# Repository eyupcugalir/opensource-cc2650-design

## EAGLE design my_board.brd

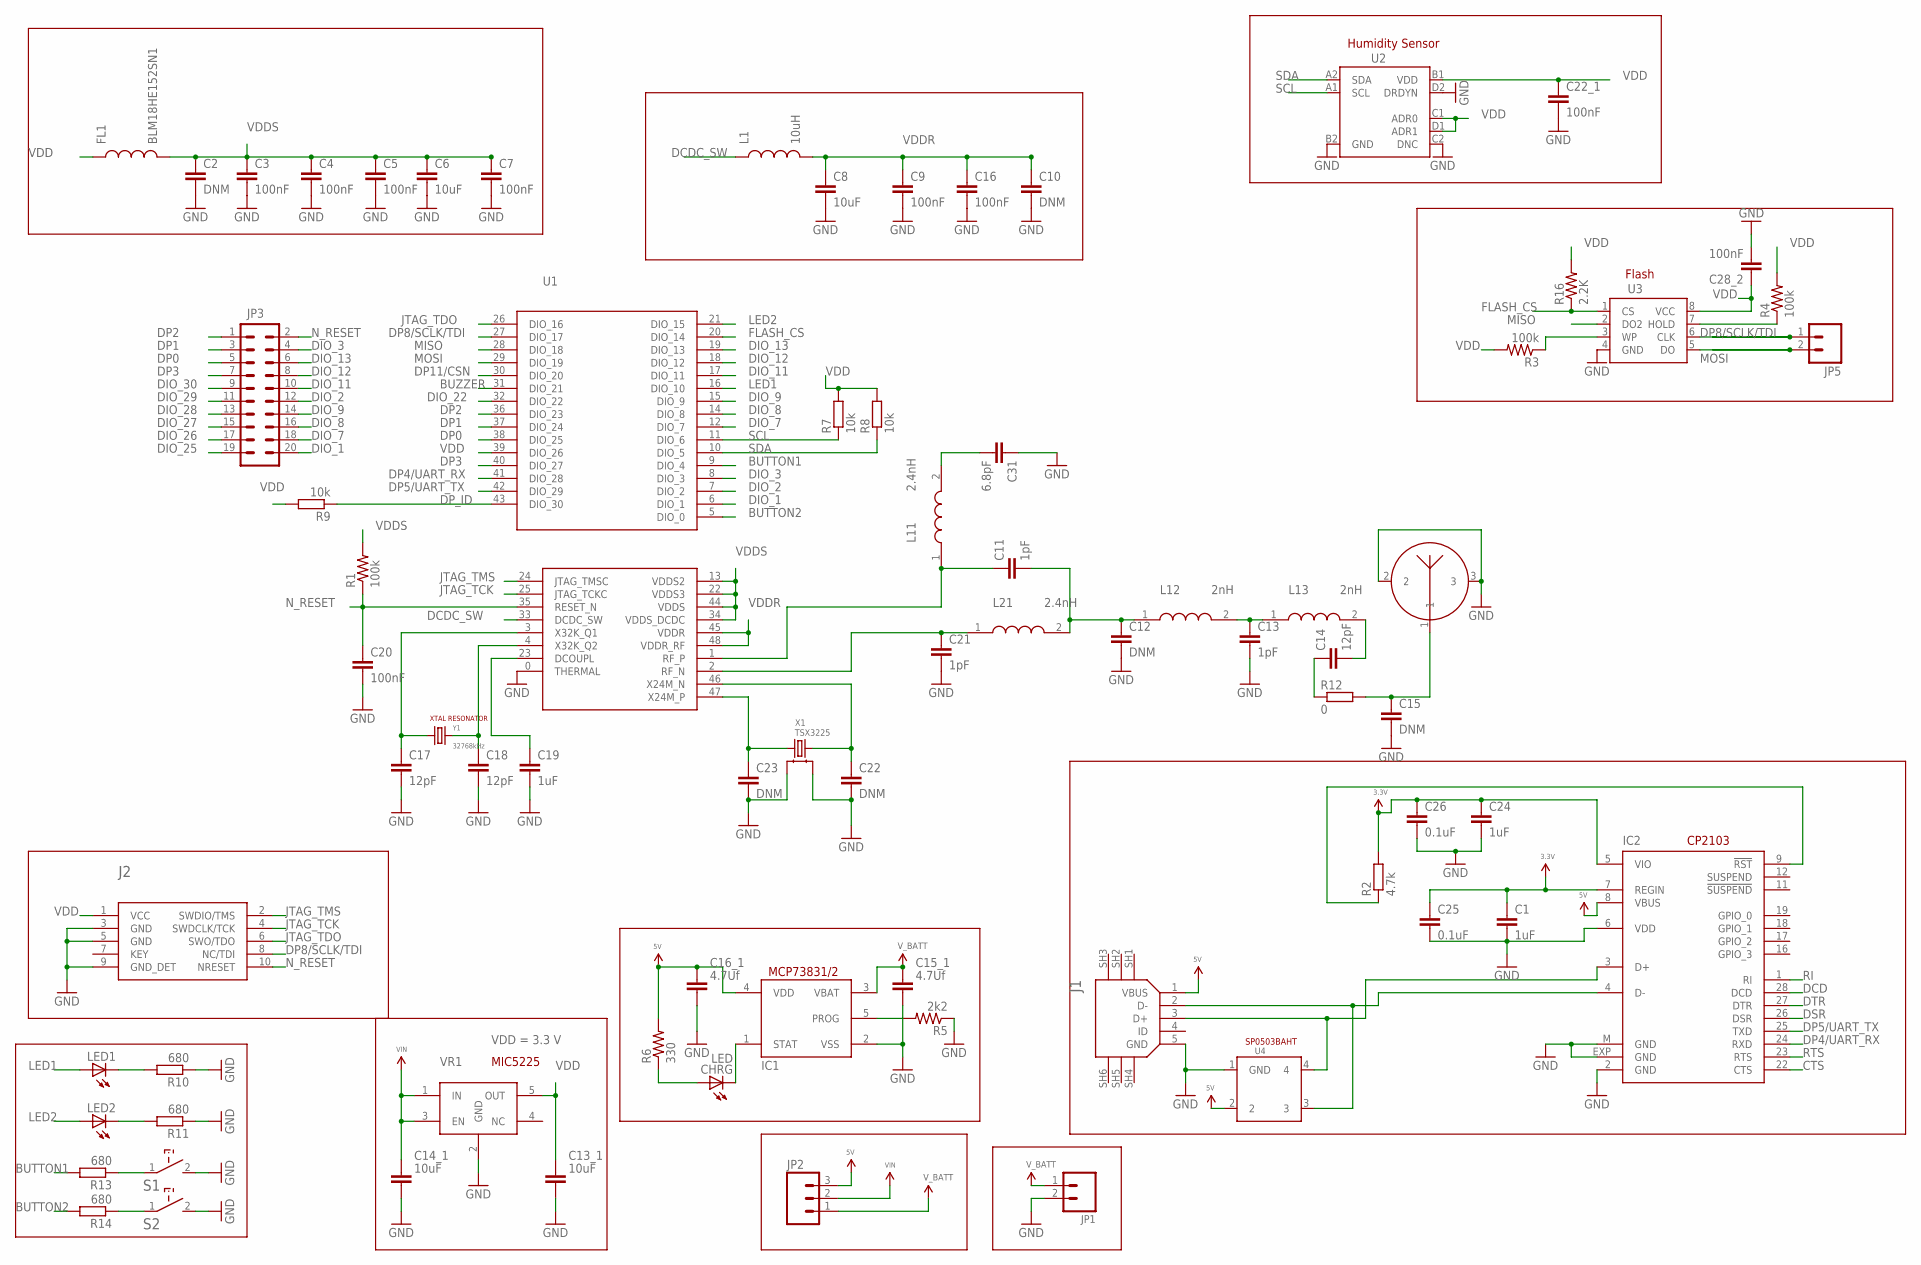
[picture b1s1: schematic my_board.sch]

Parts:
C1, C19, C24: 1uF; 0402-CAP
C2: DNM; 0603-CAP
C3, C4, C5, C9, C16, C20, C22_1, C28_2: 100nF; 0402-CAP
C6, C8: 10uF; 0603-CAP
C7: 100nF; 0603-CAP
C10, C12, C15, C22, C23: DNM; 0402-CAP
C11, C13, C21: 1pF; 0402-CAP
C13_1, C14_1: 10uF; DP_DEVICES_C603
C14, C17, C18: 12pF; 0402-CAP
C15_1, C16_1: 4.7Uf; DP_DEVICES_C603
C25, C26: 0.1uF; 0402-CAP
C31: 6.8pF; 0402-CAP
CHRG: LED; DP_DEVICES_LED-603
FL1: BLM18HE152SN1; 0603
IC1: ADAFRUIT_MCP73831/OT; ADAFRUIT_SOT23-5L
IC2: CP2103_USB_UART; MLP28
J1: USB-1981568; 1981568-1
J2: ARM-10PIN-JTAG; ARM-10PIN-DEBUGGER
JP1: SPARKFUN-CONNECTORS_M02PTH3; SPARKFUN-CONNECTORS_1X02_LONGPADS
JP2: M03-SCREW-5MM; SCREWTERMINAL-5MM-3
JP3: M10X2; 2X10
JP5: M02PTH; 1X02
L1: 10uH; 0805
L11, L21: 2.4nH; LQG15HS2N4S02D
L12, L13: 2nH; LQG15HS2N4S02D
LED1, LED2: DP_DEVICES_LED-0805; DP_DEVICES_LED-805
R1, R3, R4: 100k; 0402-RES
R2: 4.7k; R0402
R5: 2k2; SPARKFUN-RESISTORS_0805
R6: 330; SPARKFUN-RESISTORS_0805
R7, R8, R9: 10k; R0402
R10, R11, R13, R14: 680; R0402
R12: 0; R0402
R16: 2.2K; 0402-RES
S1, S2: B3U-1000P-SWITCH
U1: CC2650
U2: HDC1000YPA
U3: W25X40CLUXIGSS; W25X40SSIG
U4: SP0503BAHT
U$1: PCB-ANTENNA
VR1: USBUG_MIC5225-3.3YM5; USBUG_SOT23-5
X1: TSX3225; TSX-3225
Y1: 32768kHz; CRYSTAL_RESONATOR

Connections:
3.3V: C1.1, C24.1, C25.1, C26.1, IC2.5 (VIO), IC2.7 (REGIN), R2.2
5V: C16_1.1, IC1.4 (VDD), IC2.8 (VBUS), J1.1 (VBUS), JP2.3, R6.2, U4.2
BUTTON1: R13.2, U1.9 (DIO_4)
BUTTON2: R14.2, U1.5 (DIO_0)
BUZZER: U1.31 (DIO_21)
CTS: IC2.22 (CTS)
DCD: IC2.28 (DCD)
DCDC_SW: L1.1, U1.33 (DCDC_SW)
DIO_1: JP3.20, U1.6 (DIO_1)
DIO_2: JP3.12, U1.7 (DIO_2)
DIO_3: JP3.4, U1.8 (DIO_3)
DIO_7: JP3.18, U1.12 (DIO_7)
DIO_8: JP3.16, U1.14 (DIO_8)
DIO_9: JP3.14, U1.15 (DIO_9)
DIO_11: JP3.10, U1.17 (DIO_11)
DIO_12: JP3.8, U1.18 (DIO_12)
DIO_13: JP3.6, U1.19 (DIO_13)
DIO_22: U1.32 (DIO_22)
DIO_25: JP3.19
DIO_26: JP3.17
DIO_27: JP3.15
DIO_28: JP3.13
DIO_29: JP3.11
DIO_30: JP3.9
DP0: JP3.5, U1.38 (DIO_25)
DP1: JP3.3, U1.37 (DIO_24)
DP2: JP3.1, U1.36 (DIO_23)
DP3: JP3.7, U1.40 (DIO_27)
DP4/UART_RX: IC2.24 (RXD), U1.41 (DIO_28)
DP5/UART_TX: IC2.25 (TXD), U1.42 (DIO_29)
DP8/SCLK/TDI: J2.8 (NC/TDI), JP5.1, U1.27 (DIO_17), U3.6 (CLK)
DP11/CSN: U1.30 (DIO_20)
DP_ID: R9.1, U1.43 (DIO_30)
DSR: IC2.26 (DSR)
DTR: IC2.27 (DTR)
FLASH_CS: R16.1, U1.20 (DIO_14), U3.1 (CS)
GND: C1.2, C2.2, C3.2, C4.2, C5.2, C6.2, C7.2, C8.2, C9.2, C10.2, C12.2, C13.2, C13_1.2, C14_1.2, C15.2, C15_1.2, C16.2, C16_1.2, C17.2, C18.2, C19.2, C20.2, C21.2, C22.2, C22_1.2, C23.2, C24.2, C25.2, C26.2, C28_2.2, C31.1, IC1.2 (VSS), IC2.2 (GND), IC2.6 (VDD), IC2.EXP (GND), IC2.M (GND), J1.5 (GND), J2.3 (GND), J2.5 (GND), J2.9 (GND_DET), JP1.2, R5.1, R10.1, R11.1, S1.2, S2.2, U1.0 (THERMAL), U2.B2 (GND), U2.C2 (DNC), U2.D2 (DRDYN), U3.4 (GND), U4.1 (GND), U$1.2, U$1.3, VR1.2 (GND), X1.2, X1.4
JTAG_TCK: J2.4 (SWDCLK/TCK), U1.25 (JTAG_TCKC)
JTAG_TDO: J2.6 (SWO/TDO), U1.26 (DIO_16)
JTAG_TMS: J2.2 (SWDIO/TMS), U1.24 (JTAG_TMSC)
LED1: LED1.A, U1.16 (DIO_10)
LED2: LED2.A, U1.21 (DIO_15)
MISO: U1.28 (DIO_18), U3.2 (DO2)
MOSI: JP5.2, U1.29 (DIO_19), U3.5 (DO)
unnamed: C31.2, L11.2
unnamed: C17.1, U1.3 (X32K_Q1), Y1.P$1 (1)
unnamed: C18.1, U1.4 (X32K_Q2), Y1.P$4 (2)
unnamed: C14.2, L13.2
unnamed: C22.1, U1.46 (X24M_N), X1.3
unnamed: C11.2, C12.1, L12.1, L21.2
unnamed: CHRG.A, R6.1
unnamed: C13.1, L12.2, L13.1
unnamed: C14.1, R12.1
unnamed: C15.1, R12.2, U$1.1
unnamed: C23.1, U1.47 (X24M_P), X1.1
unnamed: CHRG.C, IC1.1 (STAT)
unnamed: C11.1, L11.1, U1.1 (RF_P)
unnamed: C21.1, L21.1, U1.2 (RF_N)
unnamed: IC1.5 (PROG), R5.2
unnamed: C19.1, U1.23 (DCOUPL)
unnamed: LED1.C, R10.2
unnamed: R3.1, U3.3 (WP)
unnamed: R4.1, U3.7 (HOLD)
unnamed: IC2.3 (D+), J1.3 (D+), U4.4
unnamed: IC2.4 (D-), J1.2 (D-), U4.3
unnamed: LED2.C, R11.2
unnamed: IC2.9 (!RST), R2.1
unnamed: R13.1, S1.1
unnamed: R14.1, S2.1
N_RESET: C20.1, J2.10 (NRESET), JP3.2, R1.1, U1.35 (RESET_N)
RI: IC2.1 (RI)
RTS: IC2.23 (RTS)
SCL: R7.1, U1.11 (DIO_6), U2.A1 (SCL)
SDA: R8.1, U1.10 (DIO_5), U2.A2 (SDA)
VDD: C13_1.1, C22_1.1, C28_2.1, FL1.1, J2.1 (VCC), R3.2, R4.2, R7.2, R8.2, R9.2, R16.2, U1.39 (DIO_26), U2.B1 (VDD), U2.C1 (ADR0), U2.D1 (ADR1), U3.8 (VCC), VR1.5 (OUT)
VDDR: C8.1, C9.1, C10.1, C16.1, L1.2, U1.45 (VDDR), U1.48 (VDDR_RF)
VDDS: C2.1, C3.1, C4.1, C5.1, C6.1, C7.1, FL1.2, R1.2, U1.13 (VDDS2), U1.22 (VDDS3), U1.34 (VDDS_DCDC), U1.44 (VDDS)
VIN: C14_1.1, JP2.2, VR1.1 (IN), VR1.3 (EN)
V_BATT: C15_1.1, IC1.3 (VBAT), JP1.1, JP2.1

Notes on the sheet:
VDD = 3.3 V

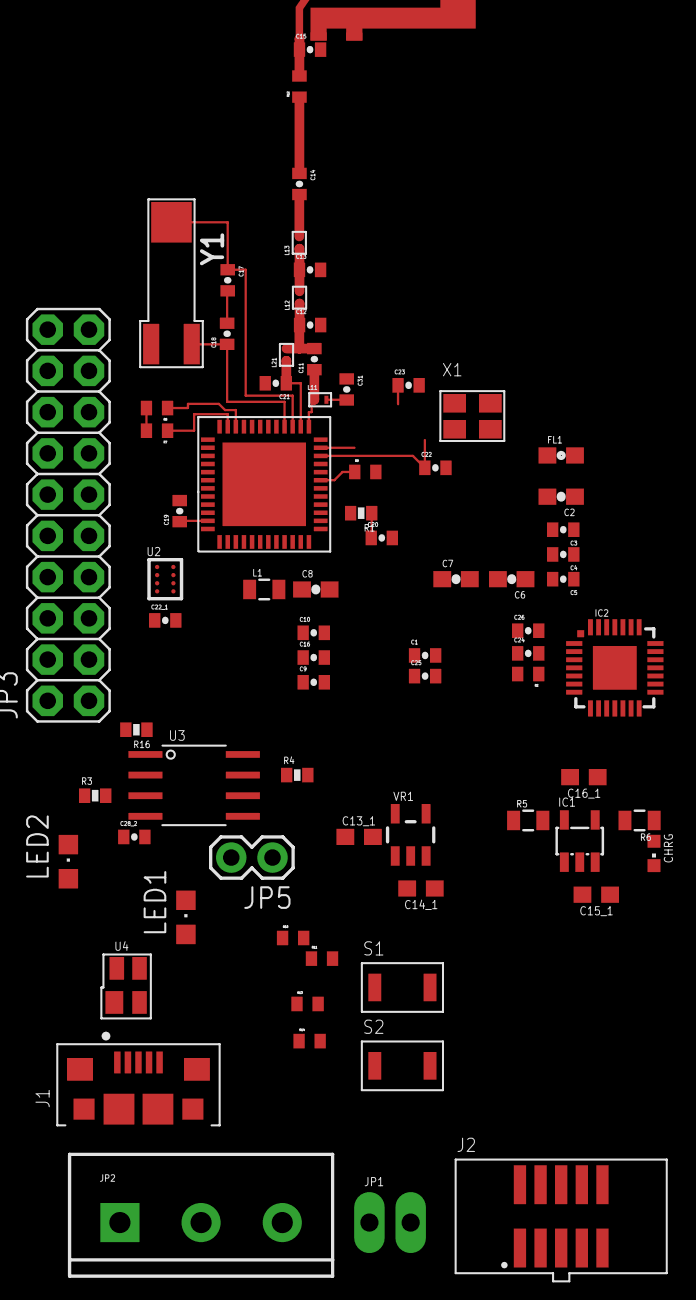
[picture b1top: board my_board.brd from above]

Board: 2 copper layers, 75 parts (0 on the bottom side), 64 nets.

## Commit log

2016-01-13 myboard

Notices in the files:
parts and their libraries:
SparkFun-Capacitors: Licensing: Creative Commons ShareAlike 4.0 International - https://creativecommons.org/licenses/by-sa/4.0
